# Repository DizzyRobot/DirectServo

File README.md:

# DirectServo
Controller that drives BLDC motor as servo

More details to come, 
for now this is just a placeholder informing that this is a motor driver microcontroller board that can be attached to a 3-phase
BLDC motor (such as a camera gimbal) and control it via RS485 protocol. 
It receives torque commands and sends back the angular position read via magnetic sensor.

[https://www.dizzy.ai/documentation/motor-driver/]

For a walk-through of manufacturing a DirectServo, programming it, and testing it, see:
/Manufacturing/README.md

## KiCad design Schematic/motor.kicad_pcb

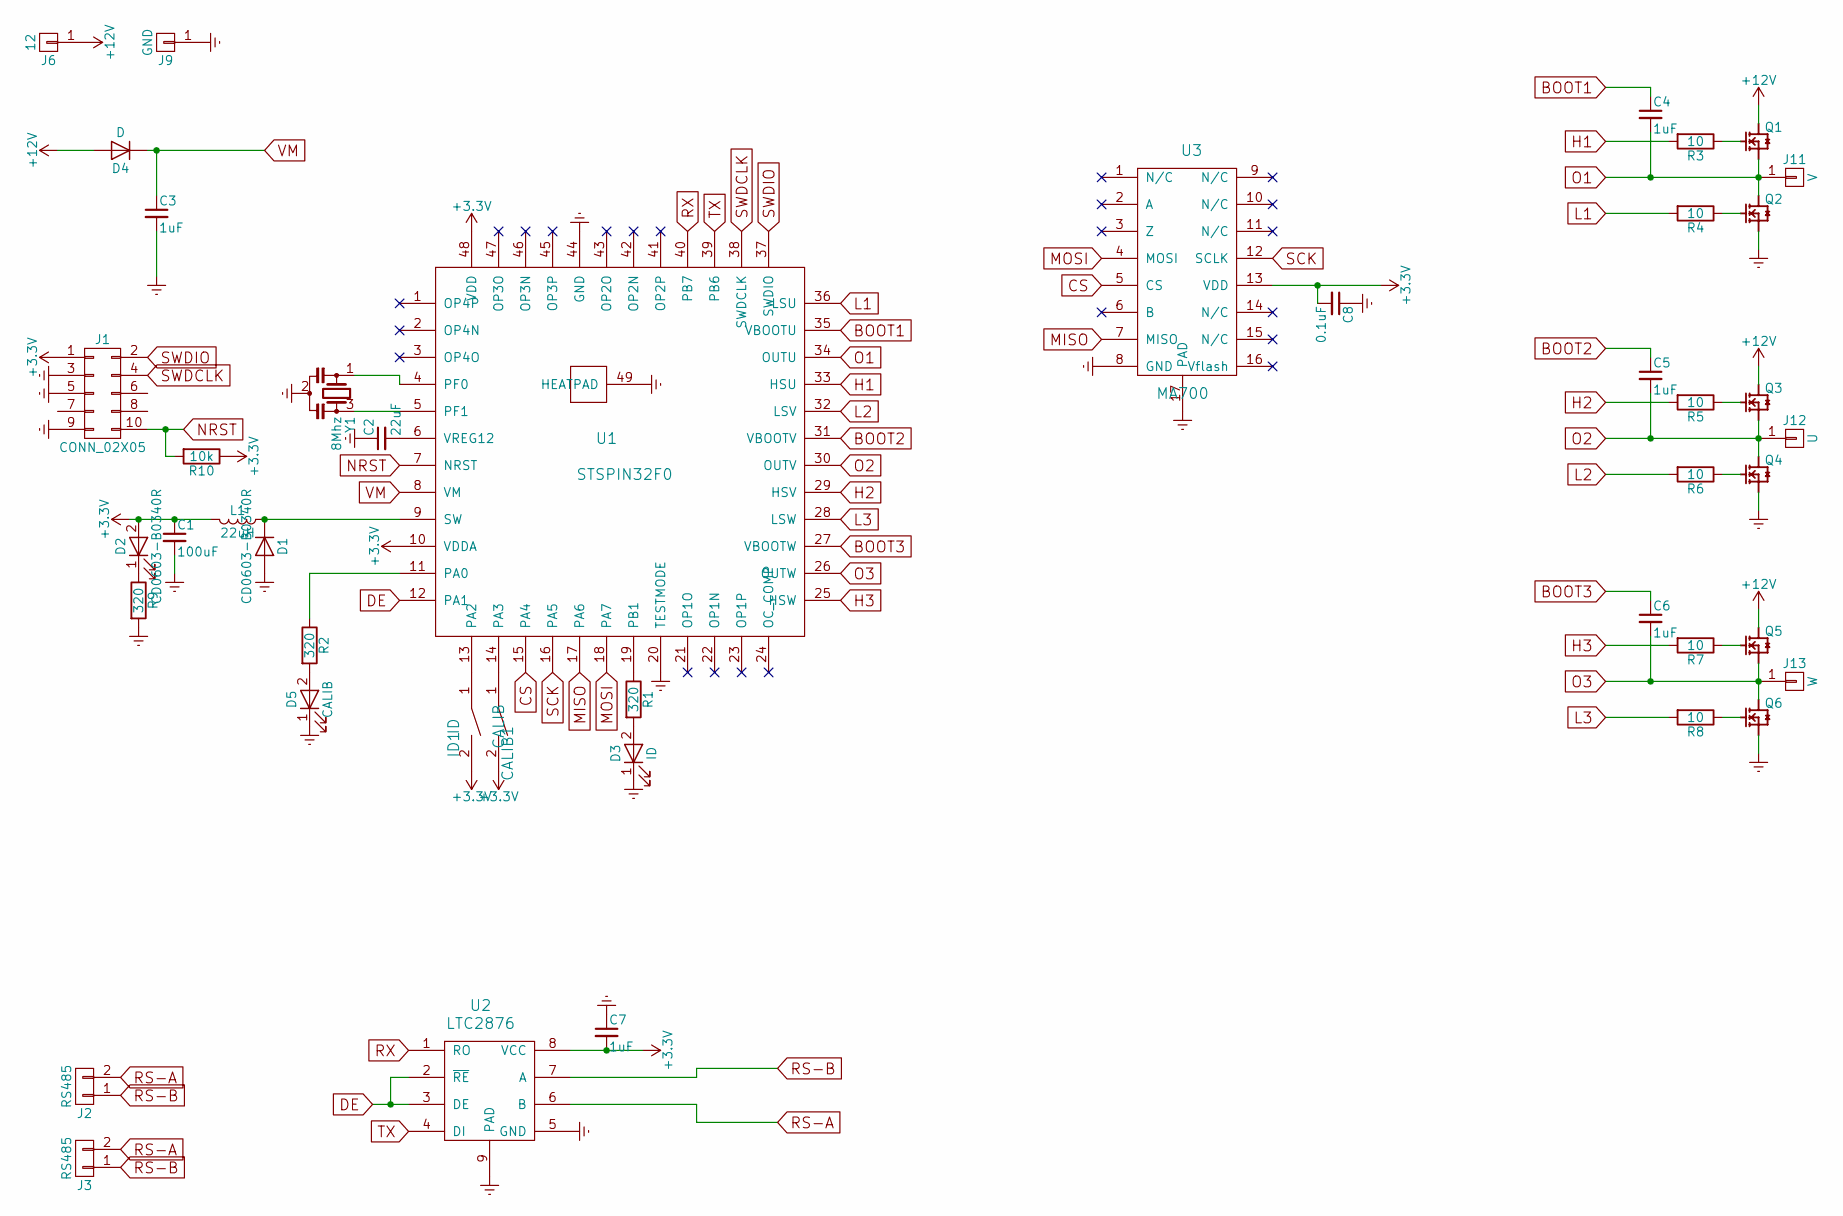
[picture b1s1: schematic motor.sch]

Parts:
C1: 100uF; C_0805
C2: 22uF; C_0805
C3: 1uF; C_1206
C4, C5, C6, C7: 1uF; C_0603
C8: 0.1uF; C_0603
CALIB1: CALIB; R_1206
D1: CD0603-B0340R; D_SOD-323F
D2: CD0603-B0340R; LED_0603
D3: ID; LED_0603
D4: D; D_SOD-323F
D5: CALIB; LED_0603
ID1: ID; R_1206
J1: CONN_02X05; Pin_Header_Straight_2x05_Pitch1.27mm_SMD
J2, J3: RS485; Pin_Header_Straight_1x02_Pitch2.54mm
J6: 12; Pin_Header_Straight_1x01_Pitch2.54mm
J9: GND; Pin_Header_Straight_1x01_Pitch2.54mm
J11: V; Pin_Header_Straight_1x01_Pitch2.54mm
J12: U; Pin_Header_Straight_1x01_Pitch2.54mm
J13: W; Pin_Header_Straight_1x01_Pitch2.54mm
L1: 22uH; L_1210
Q1, Q3, Q5: PSMN3R3-40YS
Q2, Q4, Q6: PSMN3R3-40YS; PSMN3R3-40YS-vias
R1, R2, R9: 320; R_0603
R3, R4, R5, R6, R7, R8: 10; R_0603
R10: 10k; R_0603
U1: STSPIN32F0; STSPIN32-nopad
U2: LTC2876
U3: MA700; QFN-16-1EP_3x3mm_Pitch0.5mm
Y1: 8Mhz; Oscillator

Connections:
+3V3: C1.1, C7.2, C8.2, CALIB1.2, D2.2 (A), ID1.2, J1.1, L1.2, R10.1, U1.10 (VDDA), U1.48 (VDD), U2.8 (VCC), U3.13 (VDD)
+12V: D4.2 (A), J6.1, Q1.5678 (D), Q3.5678 (D), Q5.5678 (D)
BOOT1: C4.1, U1.35 (VBOOTU)
BOOT2: C5.1, U1.31 (VBOOTV)
BOOT3: C6.1, U1.27 (VBOOTW)
CS: U1.15 (PA4), U3.5 (CS)
DE: U1.12 (PA1), U2.2 (~RE), U2.3 (DE)
Earth: C1.2, C2.1, C3.2, C7.1, C8.1, D1.2 (A), D3.1 (K), D5.1 (K), J1.3, J1.5, J1.9, J9.1, Q2.1 (S), Q2.2 (S), Q2.3 (S), Q4.1 (S), Q4.2 (S), Q4.3 (S), Q6.1 (S), Q6.2 (S), Q6.3 (S), R9.2, U1.20 (TESTMODE), U1.44 (GND), U1.49 (HEATPAD), U2.5 (GND), U2.9 (PAD), U3.8 (GND), U3.17 (PAD), Y1.2
H1: R3.2, U1.33 (HSU)
H2: R5.2, U1.29 (HSV)
H3: R7.2, U1.25 (HSW)
L1: R4.2, U1.36 (LSU)
L2: R6.2, U1.32 (LSV)
L3: R8.2, U1.28 (LSW)
MISO: U1.17 (PA6), U3.7 (MISO)
MOSI: U1.18 (PA7), U3.4 (MOSI)
NRST: J1.10, R10.2, U1.7 (NRST)
unnamed: C2.2, U1.6 (VREG12)
unnamed: CALIB1.1, U1.14 (PA3)
unnamed: D1.1 (K), L1.1, U1.9 (SW)
unnamed: D2.1 (K), R9.1
unnamed: D3.2 (A), R1.2
unnamed: D5.2 (A), R2.2
unnamed: ID1.1, U1.13 (PA2)
unnamed: Q1.4 (G), R3.1
unnamed: Q2.4 (G), R4.1
unnamed: Q3.4 (G), R5.1
unnamed: Q4.4 (G), R6.1
unnamed: Q5.4 (G), R7.1
unnamed: Q6.4 (G), R8.1
unnamed: R1.1, U1.19 (PB1)
unnamed: R2.1, U1.11 (PA0)
unnamed: U1.4 (PF0), Y1.1
unnamed: U1.5 (PF1), Y1.3
O1: C4.2, J11.1, Q1.1 (S), Q1.2 (S), Q1.3 (S), Q2.5678 (D), U1.34 (OUTU)
O2: C5.2, J12.1, Q3.1 (S), Q3.2 (S), Q3.3 (S), Q4.5678 (D), U1.30 (OUTV)
O3: C6.2, J13.1, Q5.1 (S), Q5.2 (S), Q5.3 (S), Q6.5678 (D), U1.26 (OUTW)
RS-A: J2.2, J3.2, U2.6 (B)
RS-B: J2.1, J3.1, U2.7 (A)
RX: U1.40 (PB7), U2.1 (RO)
SCK: U1.16 (PA5), U3.12 (SCLK)
SWDCLK: J1.4, U1.38 (SWDCLK)
SWDIO: J1.2, U1.37 (SWDIO)
TX: U1.39 (PB6), U2.4 (DI)
VM: C3.1, D4.1 (K), U1.8 (VM)

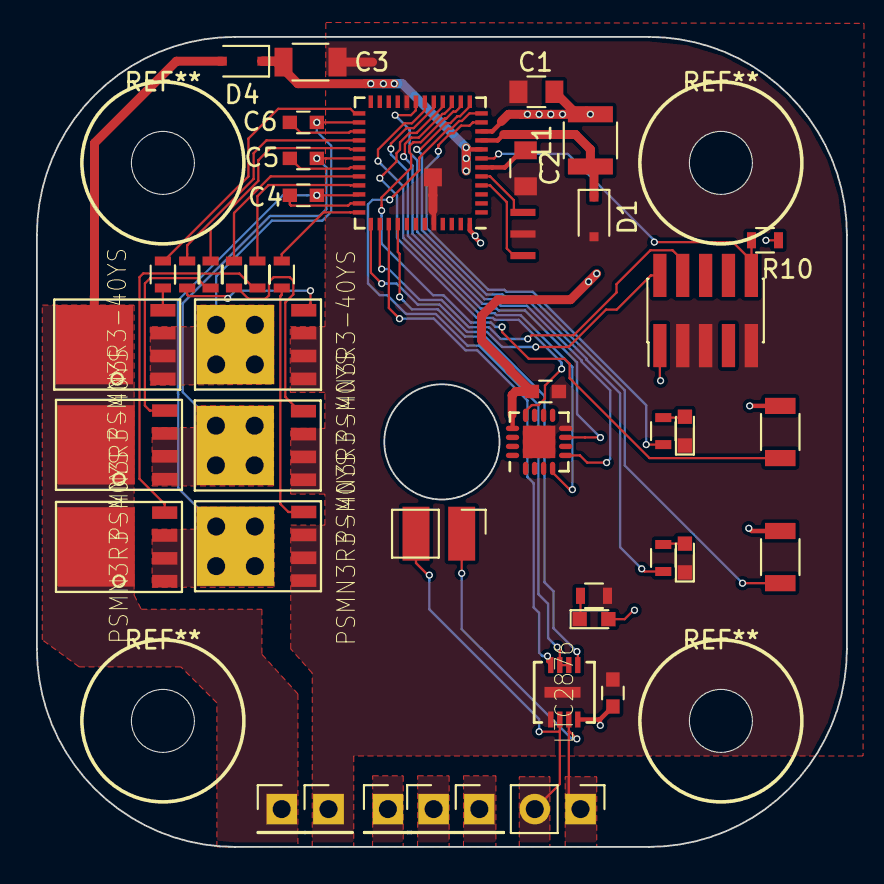
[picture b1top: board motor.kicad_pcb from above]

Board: 2 copper layers, 45.0 x 45.0 mm, 44 parts (0 on the bottom side), 45 nets.

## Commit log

2018-10-14 second commit
2018-10-14 third commit
2018-10-21 timer and power range fixes
2018-10-22 structured USART commands
2018-10-27 just started filtering and decided to save :)
2018-10-27 filtering
2018-10-27 32 quadrants
2018-10-28 fixed mag sensor pre-scale
2018-12-09 fixed hex parsing
2019-08-31 * Various formatting changes, to flow, changed some variables to fixed width integer type, made sure interrupt accessed variables were volatile, etc. * Added a failsafe angle limit feature, which is 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
2019-09-15 Added a hook for user to define additional kill on commands. As an example, for my application, this lets me remove power from the servo rail and the motors during a failure.
2019-10-05 updates to the python interface
2019-11-09 * delay_ticks() and delay_ms() added. * Response message now also includes max acceleration since last response. So sendangle is now sendstate (angle and acceleration). * Added a new set-zero-angle c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
